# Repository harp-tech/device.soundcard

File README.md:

## Harp Soundcard
This is a high performance sound card with two output channels using 24 bits DACs at 192kHz sample rate. 

### Hardware Compatibility

| HW Version | Board                    | Board HW Version  | Notes                             |
| ---------- | ------------------------ |------------------ | --------------------------------- |
| **All**    | [Peripheral.AudioAmp][1] | >= 2.0            |                                   |

[1]: https://github.com/harp-tech/peripheral.audioamp

### Firmware Compatibility

| FW Version | Board                 | Board HW Version | Notes                                   |
| ---------- | --------------------- | ---------------- | --------------------------------------- |
| **>= 2.2** | [Device.SoundCard][2] | >= 1.0           | Bpod serial communication not supported |
| **<= 2.2** | [Device.SoundCard][2] | >= 1.0           |                                         |

[2]: https://github.com/harp-tech/device.soundcard

### Key Features ###

* Internal memory to store sounds, enabling low-latency sound delivery
* Pre-selected sounds can be triggered using an external TTL
* Internal wave generator allows the user to configure a pure tone without loading a sound file
* Stereo 24 bit @ 192 kHz maximum sampling rate outputs
* THD: -111dB (1 kHz @ 2 V rms)
* Noise Floor:	20 µV rms | -94 dB (20 Hz – 80 kHz)
* SNR:	100 dB | 113 dbA (20 Hz – 80 kHz @ 2 V rms)

### Connectivity ###

* 1x clock sync input (CLKIN) [stereo jack]
* 1x USB (for computer communication) [USB Mini-B]
* 1x micro USB (for sounds loading) [USB Micro-B]
* 1x 12V supply [barrel connector jack]
* 1x reset button [tactile switch]
* 1x output for the left channel [RCA]
* 1x output for the right channel [RCA]
* 3x general purpose digital outputs (3.3V or 5V) (OUT0-OUT2) [screw terminal]
* 3x general purpose digital inputs (5V tolerant) (IN0-IN2) [screw terminal]
* 2x analog inputs (3.3V máx - 5V tolerant) (ADC0-ADC1) [screw terminal]

## Interface ##

The interface with the Harp Soundcard can be done through [Bonsai](https://bonsai-rx.org/) or a dedicated GUI (Graphical User Interface).

### Install Graphical User Interface (GUI) ###

In order to use this GUI, there are some software that needs to be installed:

1 - Install the [drivers](https://bitbucket.org/fchampalimaud/downloads/downloads/UsbDriver-2.12.26.zip).

2 - Install the [runtime](https://bitbucket.org/fchampalimaud/downloads/downloads/Runtime-1.0.zip).

3 - Reboot the computer.

4 - Install the [GUI](https://bitbucket.org/fchampalimaud/downloads/downloads/Harp%20Sound%20Card%20v1.2.1.zip).

### Install Drivers ###

To install the proper drivers to interface with the device, follow the next steps in sequence.

1 - Connect both Harp Sound Card's USB ports to the computer.

2 - Launch the previously installed Harp Sound Card GUI.

3 - Click on the button Open Drivers folder and launch the zadig-2.3.exe.

4 - (1) Select the Harp Sound Card from the list. If the device is not available, go to Options -> List All Devices.

5 - (2) Select the WinUSB driver and click Install WCID Driver.

## Firmware ##

### Tagging Scheme ###

|Tag|Description|
|-|-|
|SoundCard-*|Firmware for the sound card's microcontroller (8 bits processor)|
|SoundCard.PIC32-*|Firmware for the sound card's 32 bits processor|

### Firmware Update ###

1 - Install the [Harp Converto to CSV](https://bitbucket.org/fchampalimaud/downloads/downloads/Harp_Convert_To_CSV_v1.8.3.zip).

2 - Open the Harp Convert to CSV application and write *bootloader* under List box on the Options tab

3 - Select the correspondent COM port and then select the firmware to be loaded for both microcontrollers 

# Licensing #

Each subdirectory will contain a license or, possibly, a set of licenses if it involves both hardware and software.

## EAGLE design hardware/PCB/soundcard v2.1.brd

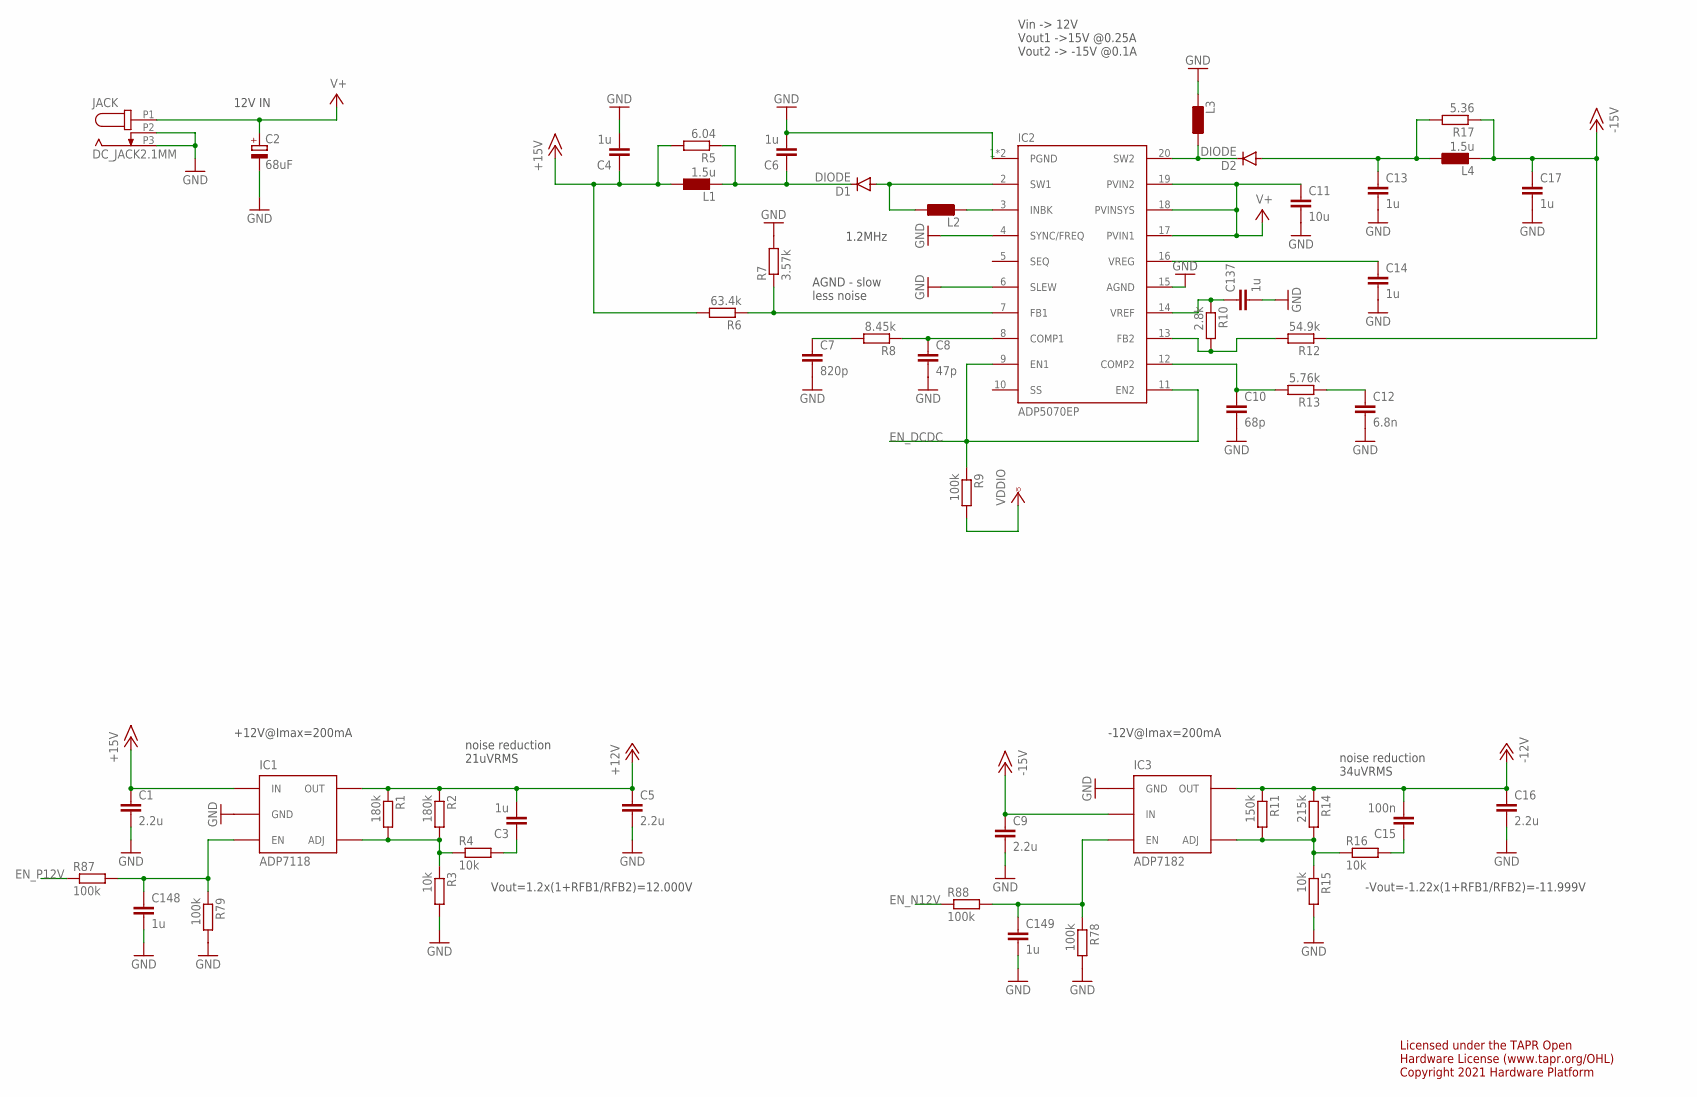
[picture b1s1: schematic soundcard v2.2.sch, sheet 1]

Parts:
C1, C5, C9, C16: 2.2u; C0603
C2: 68uF; E2-5
C3, C14, C137: 1u; C0402
C4, C6, C13, C17, C148, C149: 1u; C0603
C7: 820p; C0402
C8: 47p; C0402
C10: 68p; C0402
C11: 10u; C1206
C12: 6.8n; C0402
C15: 100n; C0402
D1, D2: DIODE; SOD-323-DIODE
IC1: ADP7118; TSOT23-5
IC2: ADP5070EP; TSSOP-EP-20
IC3: ADP7182; TSOT23-5
JACK: DC_JACK2.1MM; DC_POWER_INPUT_2.1MM
L1, L4: 1.5u; IND_LPS4012_V2
L2, L3: INDLPS6225_L; IND_LPS6225_V2
R1, R2: 180k; R0402
R3, R4, R15, R16: 10k; R0402
R5: 6.04; R0402
R6: 63.4k; R0402
R7: 3.57k; R0402
R8: 8.45k; R0402
R9, R78, R79, R87, R88: 100k; R0402
R10: 2.8k; R0402
R11: 150k; R0402
R12: 54.9k; R0402
R13: 5.76k; R0402
R14: 215k; R0402
R17: 5.36; R0402

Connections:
+12V: C3.2, C5.1, IC1.5 (OUT), R1.1, R2.1; also elsewhere on the board
+15V: C1.1, C4.1, IC1.1 (IN), L1.1, R5.2, R6.2
-12V: C15.2, C16.1, IC3.5 (OUT), R11.1, R14.1; also elsewhere on the board
-15V: C9.1, C17.1, IC3.2 (IN), L4.2, R12.1, R17.1
EN_DCDC: IC2.9 (EN1), IC2.11 (EN2), R9.1; also elsewhere on the board
EN_N12V: R88.1; also elsewhere on the board
EN_P12V: R87.1; also elsewhere on the board
GND: C1.2, C2.-, C4.2, C5.2, C6.2, C7.2, C8.2, C9.2, C10.2, C11.2, C12.2, C13.2, C14.2, C16.2, C17.2, C137.2, C148.2, C149.2, IC1.2 (GND), IC2.1 (PGND), IC2.4 (SYNC/FREQ), IC2.6 (SLEW), IC2.15 (AGND), IC2.EPAD (PGND), IC3.1 (GND), JACK.P2 (2), JACK.P3 (3), L3.2, R3.2, R7.2, R15.2, R78.2, R79.2; also elsewhere on the board
INBK: IC2.3 (INBK), L2.2
unnamed: IC2.7 (FB1), R6.1, R7.1
unnamed: C7.1, R8.2
unnamed: C8.1, IC2.8 (COMP1), R8.1
unnamed: C10.1, IC2.12 (COMP2), R13.2
unnamed: C12.1, R13.1
unnamed: C14.1, IC2.16 (VREG)
unnamed: C3.1, R4.2
unnamed: IC2.13 (FB2), R10.2, R12.2
unnamed: C137.1, IC2.14 (VREF), R10.1
unnamed: IC1.4 (ADJ), R1.2, R2.2, R3.1, R4.1
unnamed: IC3.4 (ADJ), R11.2, R14.2, R15.1, R16.1
unnamed: C15.1, R16.2
unnamed: C148.1, IC1.3 (EN), R79.1, R87.2
unnamed: C149.1, IC3.3 (EN), R78.1, R88.2
OUTN15: C13.1, D2.A, L4.1, R17.2
OUTP15: C6.1, D1.C, L1.2, R5.1
OUT_SW1: D1.A, IC2.2 (SW1), L2.1
OUT_SW2: D2.C, IC2.20 (SW2), L3.1
V+: C2.+, C11.1, IC2.17 (PVIN1), IC2.18 (PVINSYS), IC2.19 (PVIN2), JACK.P1 (1); also elsewhere on the board
VCCIO: R9.2; also elsewhere on the board

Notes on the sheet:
Vin -> 12V Vout1 ->15V @0.25A Vout2 -> -15V @0.1A
1.2MHz
AGND - slow less noise
noise reduction 34uVRMS
-12V@Imax=200mA
-Vout=-1.22x(1+RFB1/RFB2)=-11.999V
+12V@Imax=200mA
Vout=1.2x(1+RFB1/RFB2)=12.000V
noise reduction 21uVRMS
Licensed under the TAPR Open Hardware License (www.tapr.org/OHL) Copyright 2021 Hardware Platform
12V IN

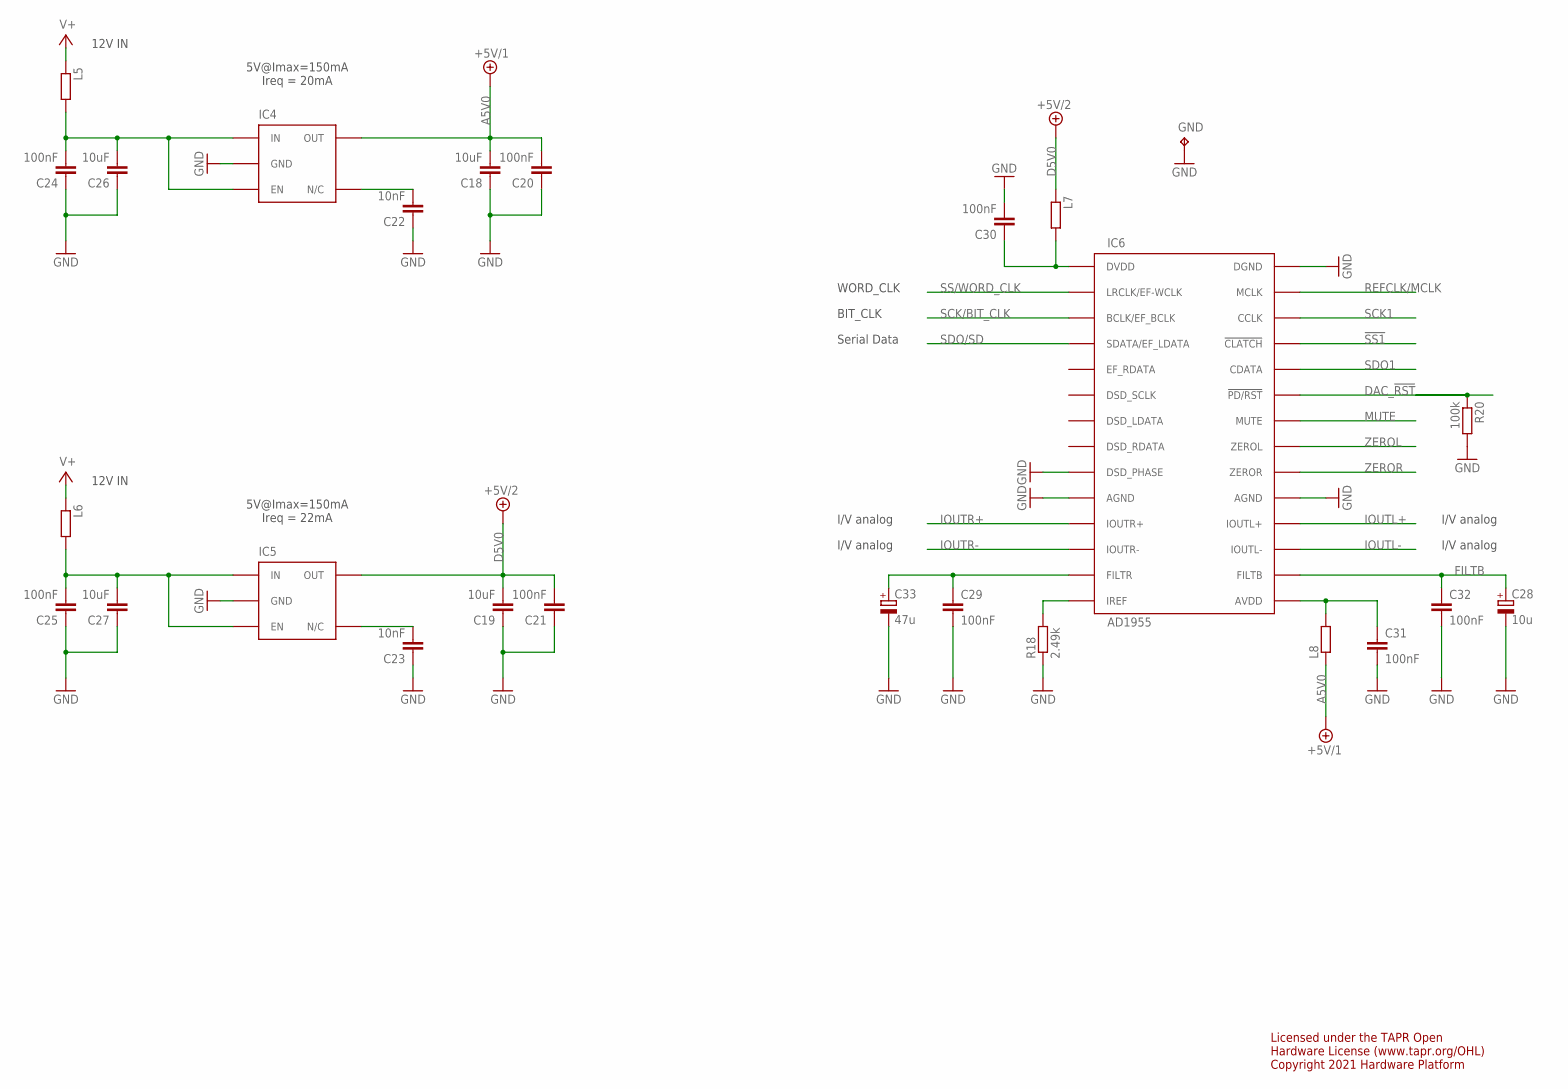
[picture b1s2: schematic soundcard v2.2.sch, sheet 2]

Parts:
C18, C19, C26, C27: 10uF; C0603
C20, C21, C24, C25, C29, C30, C31, C32: 100nF; C0402
C22, C23: 10nF; C0402
C28: 10u; B/3528-21W
C33: 47u; C/6032-28W
GND: TP; TP_1
IC4, IC5: LP5907MFX-3.3; TSOT23-5
IC6: AD1955; SSOP28
L5, L6, L7, L8: 600@100M; R0805
R18: 2.49k; R0402
R20: 100k; R0402

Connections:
!SS1: IC6.P25 (!CLATCH); also elsewhere on the board
A5V0: C18.2, C20.2, IC4.5 (OUT), L8.1; also elsewhere on the board
D5V0: C19.2, C21.2, IC5.5 (OUT), L7.1
DAC_!RST: IC6.P23 (!PD/RST), R20.1; also elsewhere on the board
FILTB: C28.+, C32.1, IC6.P16 (FILTB)
GND: C18.1, C19.1, C20.1, C21.1, C22.1, C23.1, C24.1, C25.1, C26.1, C27.1, C28.-, C29.2, C30.2, C31.2, C32.2, C33.-, GND.TP, IC4.2 (GND), IC5.2 (GND), IC6.P9 (DSD_PHASE), IC6.P10 (AGND), IC6.P19 (AGND), IC6.P28 (DGND), R18.1, R20.2; also elsewhere on the board
IOUTL+: IC6.P18 (IOUTL+); also elsewhere on the board
IOUTL-: IC6.P17 (IOUTL-); also elsewhere on the board
IOUTR+: IC6.P11 (IOUTR+); also elsewhere on the board
IOUTR-: IC6.P12 (IOUTR-); also elsewhere on the board
MUTE: IC6.P22 (MUTE); also elsewhere on the board
unnamed: C22.2, IC4.4 (N/C)
unnamed: C25.2, C27.2, IC5.1 (IN), IC5.3 (EN), L6.2
unnamed: C23.2, IC5.4 (N/C)
unnamed: C30.1, IC6.P1 (DVDD), L7.2
unnamed: C29.1, C33.+, IC6.P13 (FILTR)
unnamed: C31.1, IC6.P15 (AVDD), L8.2
unnamed: IC6.P14 (IREF), R18.2
unnamed: C24.2, C26.2, IC4.1 (IN), IC4.3 (EN), L5.2
REFCLK/MCLK: IC6.P27 (MCLK); also elsewhere on the board
SCK1: IC6.P26 (CCLK); also elsewhere on the board
SCK/BIT_CLK: IC6.P3 (BCLK/EF_BCLK); also elsewhere on the board
SDO1: IC6.P24 (CDATA); also elsewhere on the board
SDO/SD: IC6.P4 (SDATA/EF_LDATA); also elsewhere on the board
SS/WORD_CLK: IC6.P2 (LRCLK/EF-WCLK); also elsewhere on the board
V+: L5.1, L6.1; also elsewhere on the board
ZEROL: IC6.P21 (ZEROL); also elsewhere on the board
ZEROR: IC6.P20 (ZEROR); also elsewhere on the board

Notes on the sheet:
WORD_CLK
BIT_CLK
Serial Data
I/V analog
5V@Imax=150mA Ireq = 20mA
12V IN
Licensed under the TAPR Open Hardware License (www.tapr.org/OHL) Copyright 2021 Hardware Platform
5V@Imax=150mA Ireq = 22mA

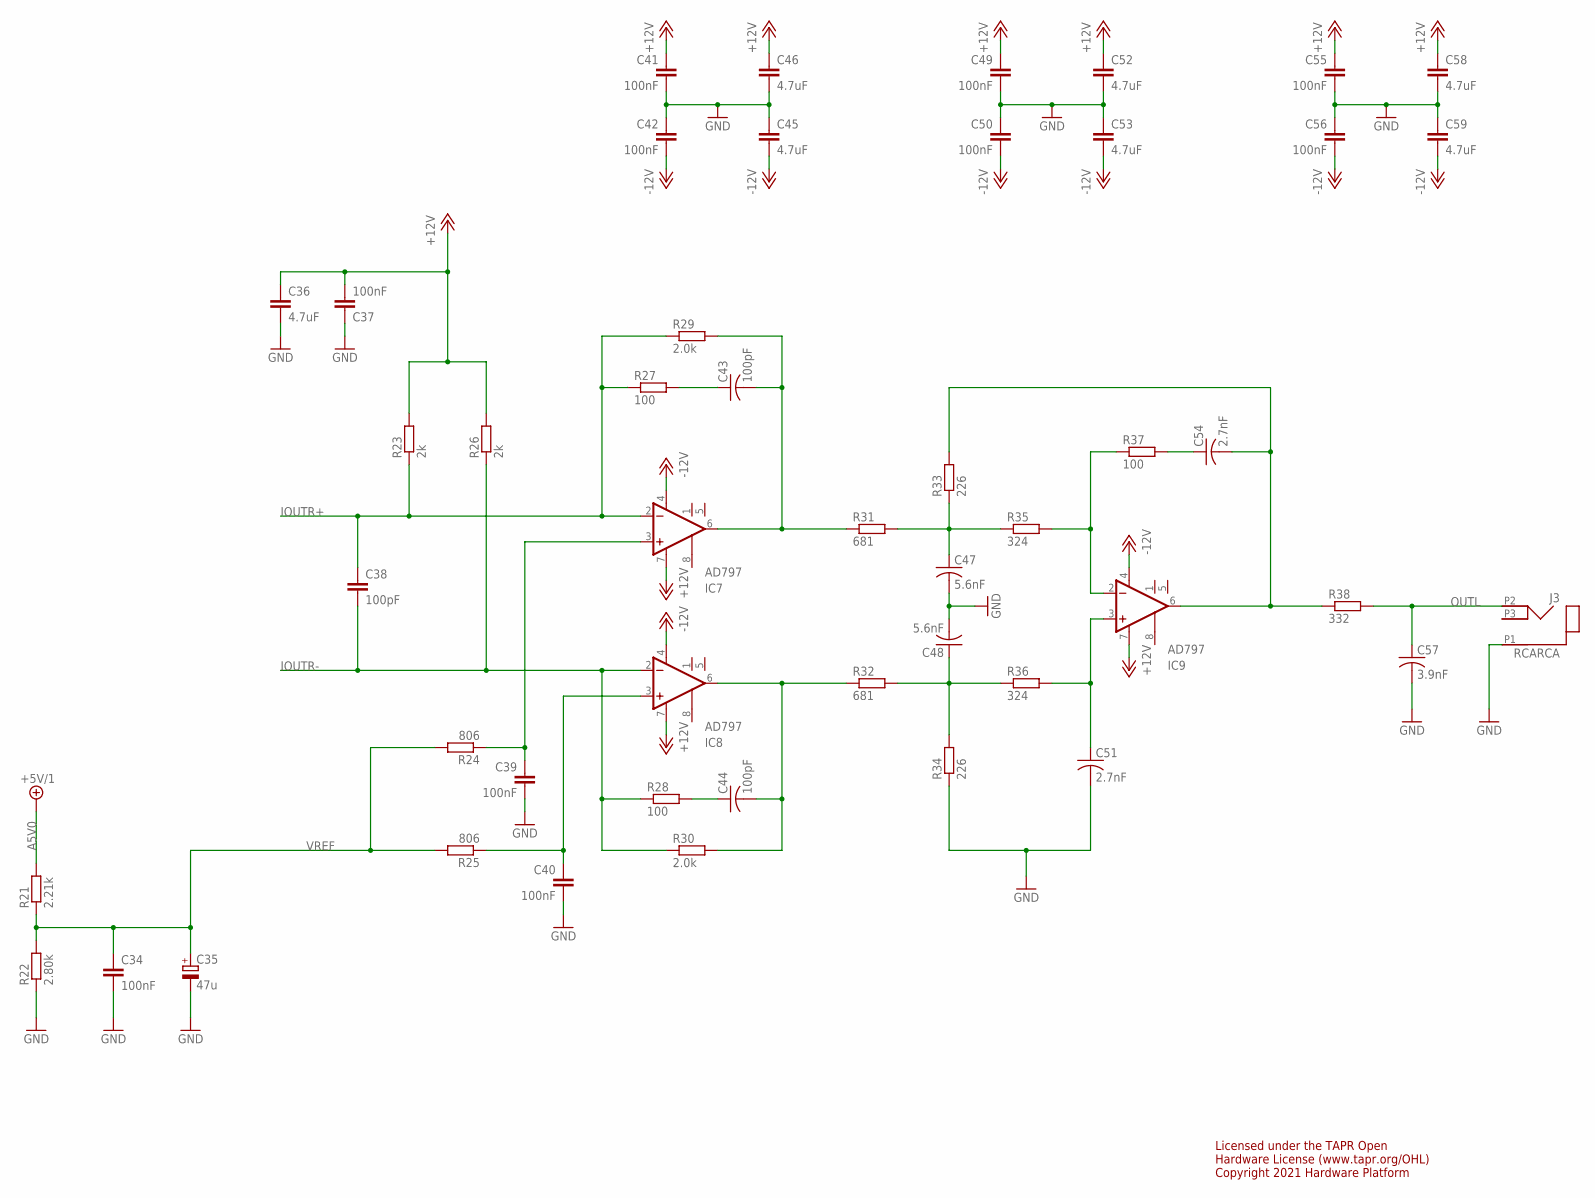
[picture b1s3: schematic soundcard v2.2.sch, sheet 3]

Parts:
C34, C37, C39, C40, C41, C42, C49, C50, C55, C56: 100nF; C0402
C35: 47u; C/6032-28W
C36, C45, C46, C52, C53, C58, C59: 4.7uF; C0603
C38: 100pF; C0603
C43, C44: 100pF; C050-025X075
C47, C48: 5.6nF; C050-025X075
C51, C54: 2.7nF; C050-025X075
C57: 3.9nF; C050-025X075
IC7, IC8, IC9: AD797; SO08
J3: RCARCA; RCA
R21: 2.21k; R0402
R22: 2.80k; R0402
R23, R26: 2k; R0402
R24, R25: 806; R0402
R27, R28, R37: 100; R0402
R29, R30: 2.0k; R0402
R31, R32: 681; R0402
R33, R34: 226; R0402
R35, R36: 324; R0402
R38: 332; R0402

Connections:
+12V: C36.1, C37.2, C41.1, C46.1, C49.1, C52.1, C55.1, C58.1, IC7.7 (V+), IC8.7 (V+), IC9.7 (V+), R23.2, R26.2; also elsewhere on the board
-12V: C42.2, C45.2, C50.2, C53.2, C56.2, C59.2, IC7.4 (V-), IC8.4 (V-), IC9.4 (V-); also elsewhere on the board
A5V0: R21.2; also elsewhere on the board
GND: C34.2, C35.-, C36.2, C37.1, C39.2, C40.2, C41.2, C42.1, C45.1, C46.2, C47.2, C48.2, C49.2, C50.1, C51.2, C52.2, C53.1, C55.2, C56.1, C57.2, C58.2, C59.1, J3.P1 (1), R22.1, R34.1; also elsewhere on the board
IOUTR+: C38.1, IC7.2 (-IN), R23.1, R27.1, R29.1; also elsewhere on the board
IOUTR-: C38.2, IC8.2 (-IN), R26.1, R28.1, R30.1; also elsewhere on the board
unnamed: C39.1, IC7.3 (+IN), R24.1
unnamed: C40.1, IC8.3 (+IN), R25.1
unnamed: C54.1, R37.2
unnamed: C44.2, IC8.6 (OUT), R30.2, R32.1
unnamed: C43.2, IC7.6 (OUT), R29.2, R31.1
unnamed: C47.1, R31.2, R33.1, R35.1
unnamed: C48.1, R32.2, R34.2, R36.1
unnamed: IC9.2 (-IN), R35.2, R37.1
unnamed: C51.1, IC9.3 (+IN), R36.2
unnamed: C54.2, IC9.6 (OUT), R33.2, R38.1
unnamed: C43.1, R27.2
unnamed: C44.1, R28.2
OUTL: C57.1, J3.P2 (2), R38.2
VREF: C34.1, C35.+, R21.1, R22.2, R24.2, R25.2; also elsewhere on the board

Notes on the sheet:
Licensed under the TAPR Open Hardware License (www.tapr.org/OHL) Copyright 2021 Hardware Platform

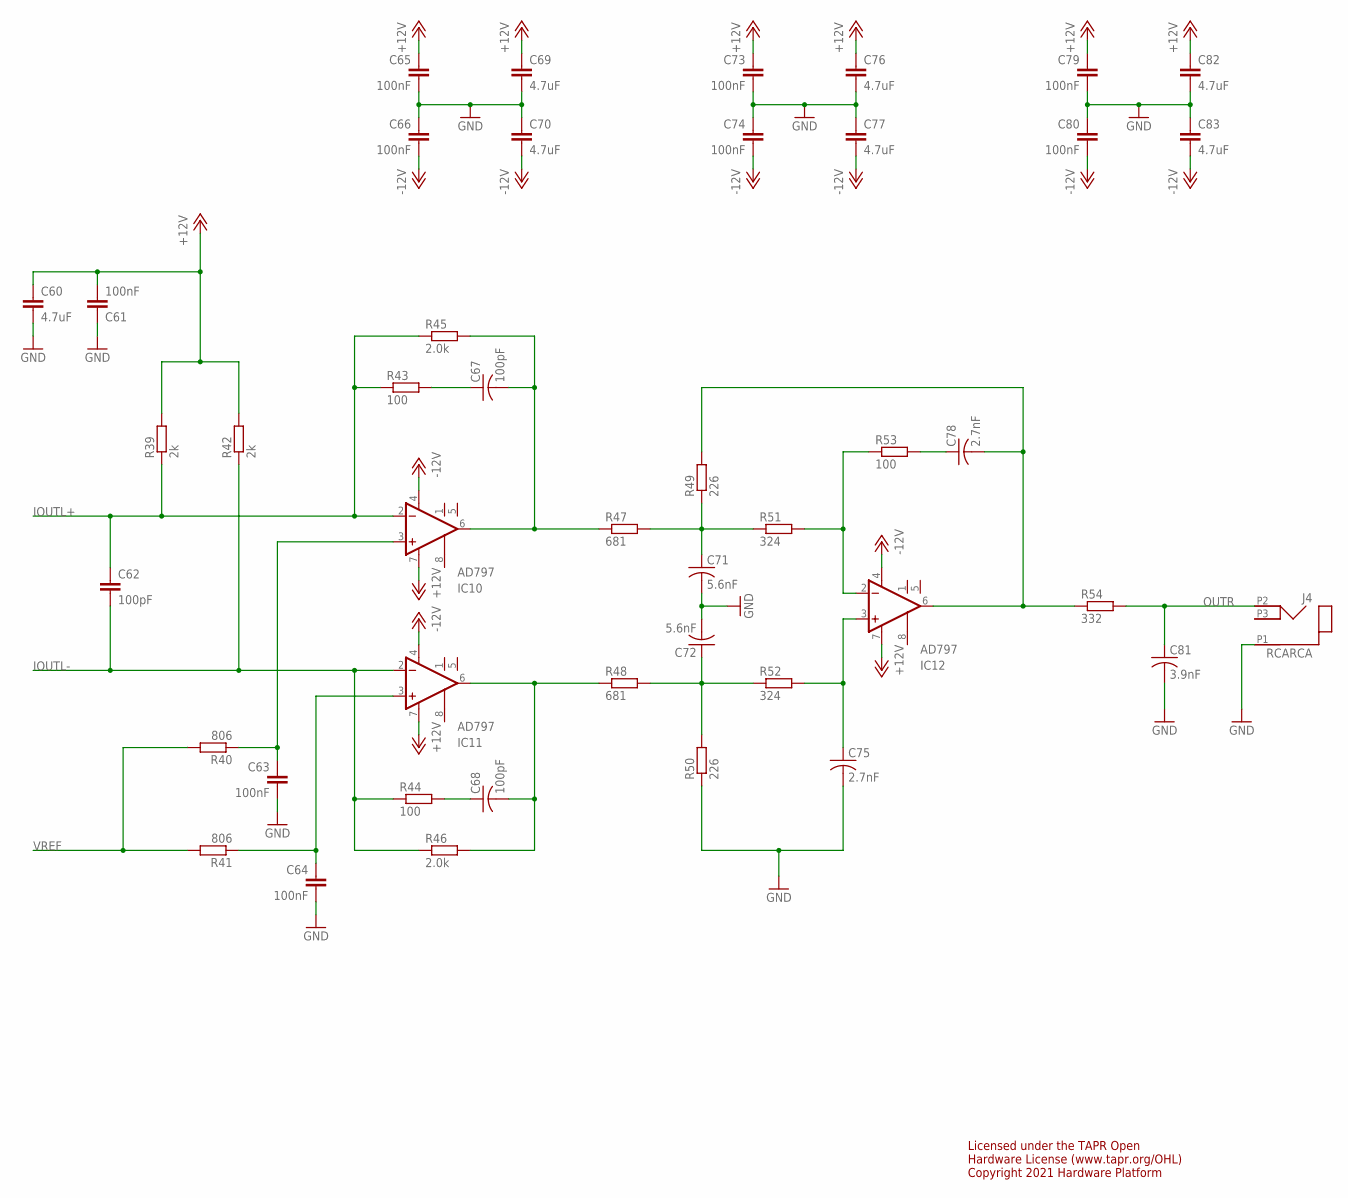
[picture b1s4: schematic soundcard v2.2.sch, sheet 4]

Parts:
C60, C69, C70, C76, C77, C82, C83: 4.7uF; C0603
C61, C63, C64, C65, C66, C73, C74, C79, C80: 100nF; C0402
C62: 100pF; C0603
C67, C68: 100pF; C050-025X075
C71, C72: 5.6nF; C050-025X075
C75, C78: 2.7nF; C050-025X075
C81: 3.9nF; C050-025X075
IC10, IC11, IC12: AD797; SO08
J4: RCARCA; RCA
R39, R42: 2k; R0402
R40, R41: 806; R0402
R43, R44, R53: 100; R0402
R45, R46: 2.0k; R0402
R47, R48: 681; R0402
R49, R50: 226; R0402
R51, R52: 324; R0402
R54: 332; R0402

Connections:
+12V: C60.1, C61.2, C65.1, C69.1, C73.1, C76.1, C79.1, C82.1, IC10.7 (V+), IC11.7 (V+), IC12.7 (V+), R39.2, R42.2; also elsewhere on the board
-12V: C66.2, C70.2, C74.2, C77.2, C80.2, C83.2, IC10.4 (V-), IC11.4 (V-), IC12.4 (V-); also elsewhere on the board
GND: C60.2, C61.1, C63.2, C64.2, C65.2, C66.1, C69.2, C70.1, C71.2, C72.2, C73.2, C74.1, C75.2, C76.2, C77.1, C79.2, C80.1, C81.2, C82.2, C83.1, J4.P1 (1), R50.1; also elsewhere on the board
IOUTL+: C62.1, IC10.2 (-IN), R39.1, R43.1, R45.1; also elsewhere on the board
IOUTL-: C62.2, IC11.2 (-IN), R42.1, R44.1, R46.1; also elsewhere on the board
unnamed: C63.1, IC10.3 (+IN), R40.1
unnamed: C67.2, IC10.6 (OUT), R45.2, R47.1
unnamed: C68.2, IC11.6 (OUT), R46.2, R48.1
unnamed: C71.1, R47.2, R49.1, R51.1
unnamed: C72.1, R48.2, R50.2, R52.1
unnamed: IC12.2 (-IN), R51.2, R53.1
unnamed: C75.1, IC12.3 (+IN), R52.2
unnamed: C78.2, IC12.6 (OUT), R49.2, R54.1
unnamed: C67.1, R43.2
unnamed: C68.1, R44.2
unnamed: C64.1, IC11.3 (+IN), R41.1
unnamed: C78.1, R53.2
OUTR: C81.1, J4.P2 (2), R54.2
VREF: R40.2, R41.2; also elsewhere on the board

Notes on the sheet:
Licensed under the TAPR Open Hardware License (www.tapr.org/OHL) Copyright 2021 Hardware Platform

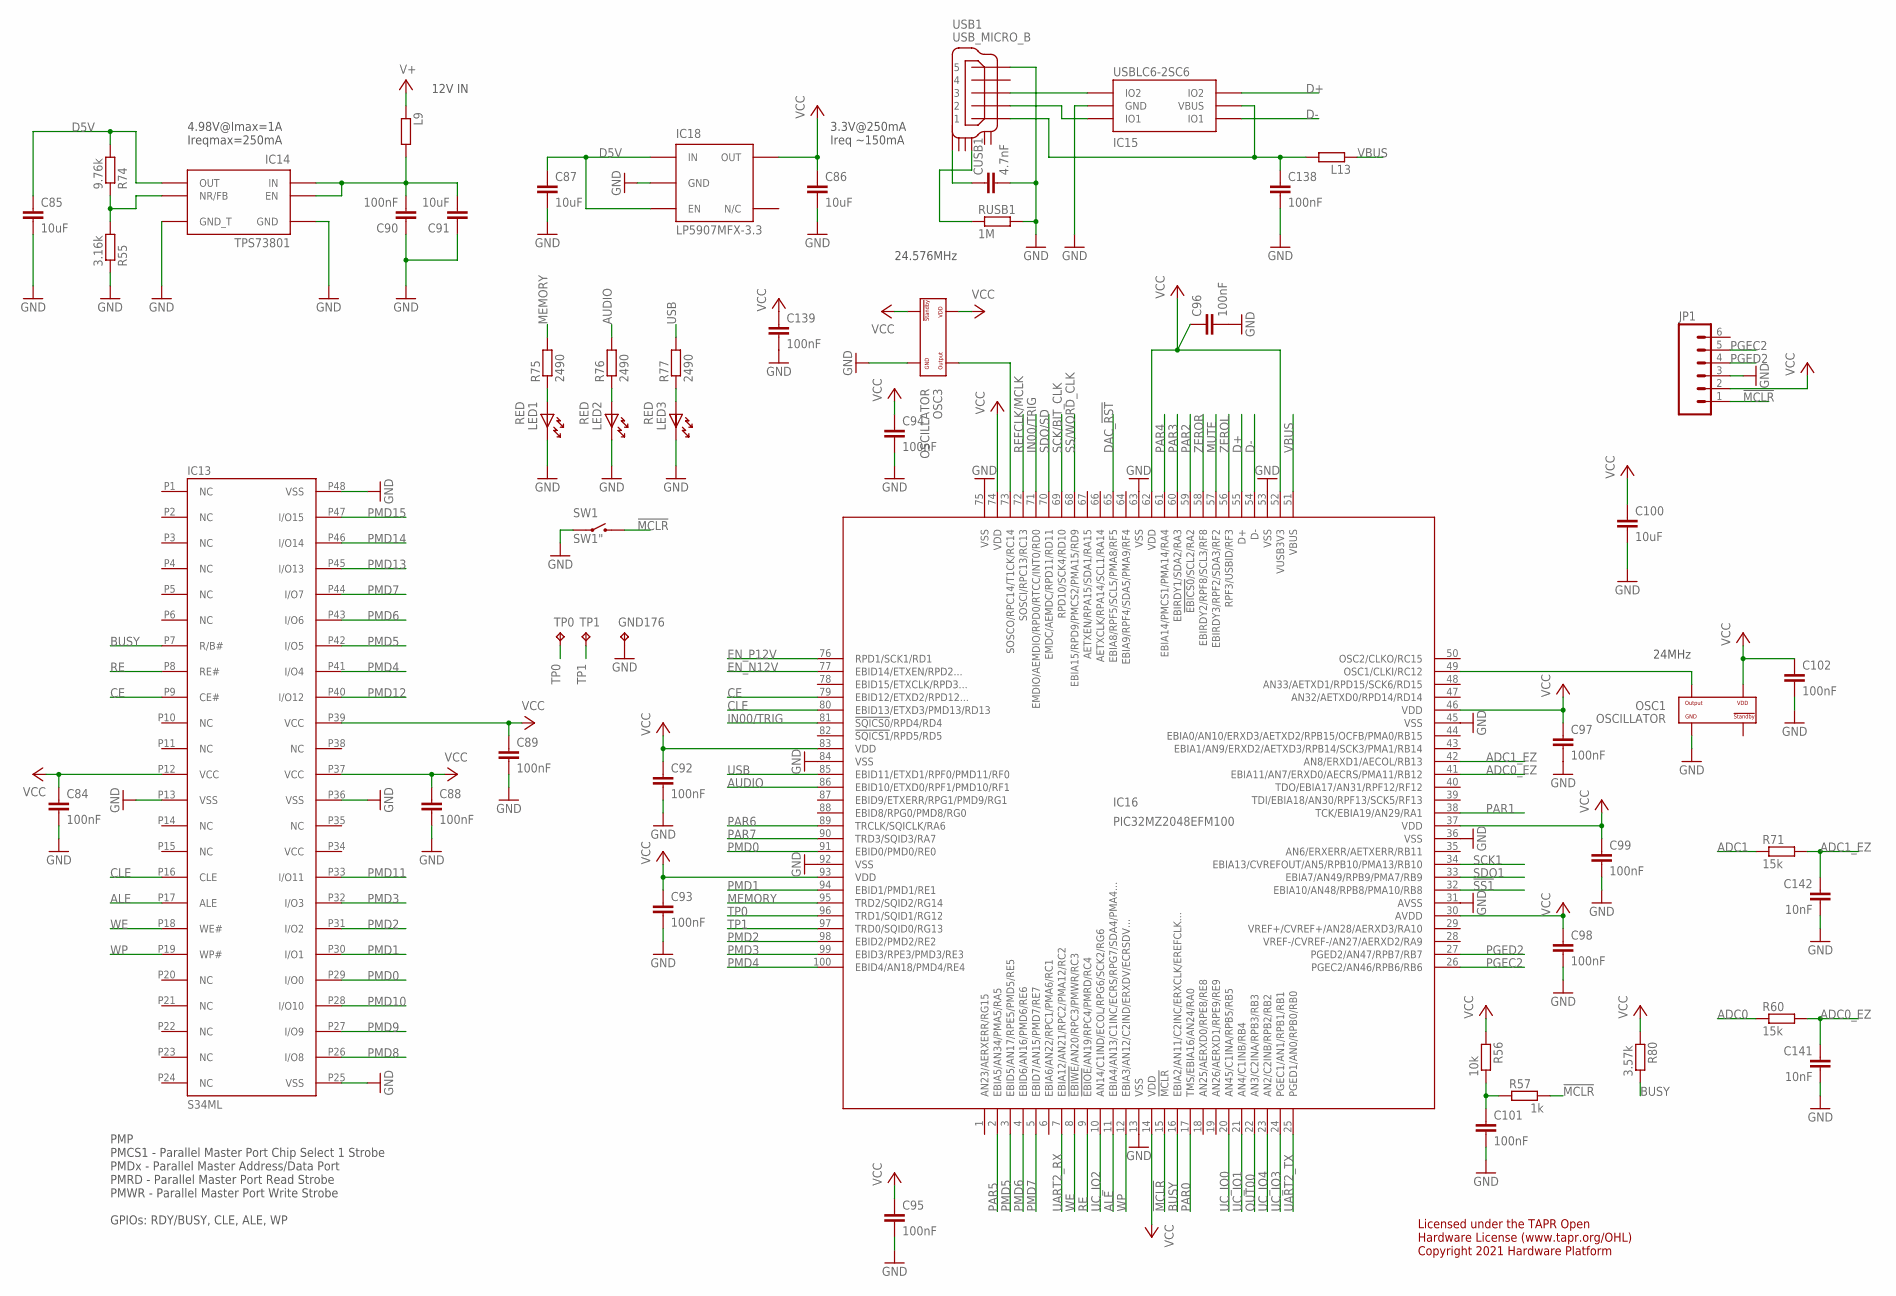
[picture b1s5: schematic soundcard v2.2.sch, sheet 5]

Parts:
C84, C88, C89, C90, C92, C93, C94, C95, C96, C97, C98, C99, C101, C102, C138, C139: 100nF; C0402
C85, C86, C87, C91, C100: 10uF; C0603
C141, C142: 10nF; C0402
CUSB1: 4.7nF; C0402
GND176: TP; TP_1
IC13: S34ML; TSOP-48
IC14: TPS73801; SOT223-6
IC15: USBLC6-2SC6; SOT23-6L
IC16: PIC32MZ2048EFM100; TQFP-100
IC18: LP5907MFX-3.3; TSOT23-5
JP1: M06NO_SILK; 1X06_NO_SILK
L9: 600@100M; R0805
L13: ???; R0805
LED1, LED2, LED3: RED; LED_HAND
OSC1, OSC3: OSCILLATOR; OSCILLATOR_3.2X2.5
R55: 3.16k; R0402
R56: 10k; R0402
R57: 1k; R0402
R60, R71: 15k; R0402
R74: 9.76k; R0402
R75, R76, R77: 2490; R0402
R80: 3.57k; R0402
RUSB1: 1M; R0402
SW1: SW1"; SWITCH_KSS
TP0, TP1: TP; TP_1
USB1: USB_MICRO_B; ZX62D-B-5P8

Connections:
!MCLR: IC16.15 (!MCLR), JP1.1, R57.1, SW1.O
!SS1: IC16.32 (EBIA10/AN48/RPB8/PMA10/RB8); also elsewhere on the board
ADC0: R60.1; also elsewhere on the board
ADC0_EZ: C141.1, IC16.41 (EBIA11/AN7/ERXD0/AECRS/PMA11/RB12), R60.2
ADC1: R71.1; also elsewhere on the board
ADC1_EZ: C142.1, IC16.42 (AN8/ERXD1/AECOL/RB13), R71.2
ALE: IC13.P17 (ALE), IC16.11 (EBIA4/AN13/C1INC/ECRS/RPG7/SDA4/PMA4...)
AUDIO: IC16.86 (EBID10/ETXD0/RPF1/PMD10/RF1), R76.2
BUSY: IC13.P7 (R/B#), IC16.16 (EBIA2/AN11/C2INC/ERXCLK/EREFCLK...), R80.1
CE: IC13.P9 (CE#), IC16.79 (EBID12/ETXD2/RPD12...)
CLE: IC13.P16 (CLE), IC16.80 (EBID13/ETXD3/PMD13/RD13)
D+: IC15.P$4 (IO2), IC16.55 (D+)
D-: IC15.P$6 (IO1), IC16.54 (D-)
DAC_!RST: IC16.65 (EBIA8/RPF5/SCL5/PMA8/RF5); also elsewhere on the board
EN_N12V: IC16.77 (EBID14/ETXEN/RPD2...); also elsewhere on the board
EN_P12V: IC16.76 (RPD1/SCK1/RD1); also elsewhere on the board
GND: C84.2, C85.2, C86.2, C87.2, C88.2, C89.2, C90.1, C91.1, C92.2, C93.2, C94.2, C95.2, C96.2, C97.2, C98.2, C99.2, C100.2, C101.2, C102.2, C138.2, C139.2, C141.2, C142.2, CUSB1.2, GND176.TP, IC13.P13 (VSS), IC13.P25 (VSS), IC13.P36 (VSS), IC13.P48 (VSS), IC14.P$3 (GND), IC14.P$6 (GND_T), IC15.P$2 (GND), IC16.13 (VSS), IC16.31 (AVSS), IC16.36 (VSS), IC16.45 (VSS), IC16.53 (VSS), IC16.63 (VSS), IC16.75 (VSS), IC16.84 (VSS), IC16.92 (VSS), IC18.2 (GND), JP1.3, LED1.K, LED2.K, LED3.K, OSC1.P$2 (GND), OSC3.P$2 (GND), R55.1, RUSB1.2, SW1.P, USB1.P$5 (5); also elsewhere on the board
IN00/TRIG: IC16.71 (EMDIO/AEMDIO/RPD0/RTCC/INT0/RD0), IC16.81 (!SQICS0!/RPD4/RD4); also elsewhere on the board
MEMORY: IC16.95 (TRD2/SQID2/RG14), R75.2
MUTE: IC16.57 (EBIRDY3/RPF2/SDA3/RF2); also elsewhere on the board
unnamed: IC14.P$4 (NR/FB), R55.2, R74.1
unnamed: C90.2, C91.2, IC14.P$1 (IN), IC14.P$5 (EN), L9.2
unnamed: IC16.73 (SOSCO/RPC14/T1CK/RC14), OSC3.P$3 (OUTPUT)
unnamed: LED1.A, R75.1
unnamed: LED2.A, R76.1
unnamed: LED3.A, R77.1
unnamed: IC16.49 (OSC1/CLKI/RC12), OSC1.P$3 (OUTPUT)
unnamed: IC15.P$1 (IO1), USB1.P$2 (2)
unnamed: IC15.P$3 (IO2), USB1.P$3 (3)
unnamed: CUSB1.1, USB1.SHIELD_4
unnamed: RUSB1.1, USB1.SHIELD_3
unnamed: C101.1, R56.1, R57.2
OUT00: IC16.22 (AN3/C2INA/RPB3/RB3); also elsewhere on the board
PAR0: IC16.17 (TMS/EBIA16/AN24/RA0); also elsewhere on the board
PAR1: IC16.38 (TCK/EBIA19/AN29/RA1); also elsewhere on the board
PAR2: IC16.59 (!EBICS0!/SCL2/RA2); also elsewhere on the board
PAR3: IC16.60 (EBIRDY1/SDA2/RA3); also elsewhere on the board
PAR4: IC16.61 (EBIA14/PMCS1/PMA14/RA4); also elsewhere on the board
PAR5: IC16.2 (EBIA5/AN34/PMA5/RA5); also elsewhere on the board
PAR6: IC16.89 (TRCLK/SQICLK/RA6); also elsewhere on the board
PAR7: IC16.90 (TRD3/SQID3/RA7); also elsewhere on the board
PGEC2: IC16.26 (PGEC2/AN46/RPB6/RB6), JP1.5
PGED2: IC16.27 (PGED2/AN47/RPB7/RB7), JP1.4
PMD0: IC13.P29 (I/O0), IC16.91 (EBID0/PMD0/RE0)
PMD1: IC13.P30 (I/O1), IC16.94 (EBID1/PMD1/RE1)
PMD2: IC13.P31 (I/O2), IC16.98 (EBID2/PMD2/RE2)
PMD3: IC13.P32 (I/O3), IC16.99 (EBID3/RPE3/PMD3/RE3)
PMD4: IC13.P41 (I/O4), IC16.100 (EBID4/AN18/PMD4/RE4)
PMD5: IC13.P42 (I/O5), IC16.3 (EBID5/AN17/RPE5/PMD5/RE5)
PMD6: IC13.P43 (I/O6), IC16.4 (EBID6/AN16/PMD6/RE6)
PMD7: IC13.P44 (I/O7), IC16.5 (EBID7/AN15/PMD7/RE7)
PMD8: IC13.P26 (I/O8)
PMD9: IC13.P27 (I/O9)
PMD10: IC13.P28 (I/O10)
PMD11: IC13.P33 (I/O11)
PMD12: IC13.P40 (I/O12)
PMD13: IC13.P45 (I/O13)
PMD14: IC13.P46 (I/O14)
PMD15: IC13.P47 (I/O15)
RE: IC13.P8 (RE#), IC16.9 (!EBIOE!/AN19/RPC4/PMRD/RC4)
REFCLK/MCLK: IC16.72 (SOSCI/RPC13/RC13); also elsewhere on the board
SCK1: IC16.34 (EBIA13/CVREFOUT/AN5/RPB10/PMA13/RB10); also elsewhere on the board
SCK/BIT_CLK: IC16.69 (RPD10/SCK4/RD10); also elsewhere on the board
SDO1: IC16.33 (EBIA7/AN49/RPB9/PMA7/RB9); also elsewhere on the board
SDO/SD: IC16.70 (EMDC/AEMDC/RPD11/RD11); also elsewhere on the board
SS/WORD_CLK: IC16.68 (EBIA15/RPD9/PMCS2/PMA15/RD9); also elsewhere on the board
TP0: IC16.96 (TRD1/SQID1/RG12), TP0.TP
TP1: IC16.97 (TRD0/SQID0/RG13), TP1.TP
UART2_RX: IC16.7 (EBIA12/AN21/RPC2/PMA12/RC2); also elsewhere on the board
UART2_TX: IC16.25 (PGED1/AN0/RPB0/RB0); also elsewhere on the board
UC_IO0: IC16.20 (AN45/C1INA/RPB5/RB5); also elsewhere on the board
UC_IO1: IC16.21 (AN4/C1INB/RB4); also elsewhere on the board
UC_IO2: IC16.10 (AN14/C1IND/ECOL/RPG6/SCK2/RG6); also elsewhere on the board
UC_IO3: IC16.24 (PGEC1/AN1/RPB1/RB1); also elsewhere on the board
UC_IO4: IC16.23 (AN2/C2INB/RPB2/RB2); also elsewhere on the board
USB: IC16.85 (EBID11/ETXD1/RPF0/PMD11/RF0), R77.2
V+: L9.1; also elsewhere on the board
VBUS: IC16.51 (VBUS), L13.1
VBUSX: C138.1, IC15.P$5 (VBUS), L13.2, USB1.P$1 (1)
VCC: C84.1, C86.1, C88.1, C89.1, C92.1, C93.1, C94.1, C95.1, C96.1, C97.1, C98.1, C99.1, C100.1, C102.1, C139.1, IC13.P12 (VCC), IC13.P37 (VCC), IC13.P39 (VCC), IC16.14 (VDD), IC16.30 (AVDD), IC16.37 (VDD), IC16.46 (VDD), IC16.52 (VUSB3V3), IC16.62 (VDD), IC16.74 (VDD), IC16.83 (VDD), IC16.93 (VDD), IC18.5 (OUT), JP1.2, OSC1.P$4 (VDD), OSC3.P$1 (STANDBY#), OSC3.P$4 (VDD), R56.2, R80.2
WE: IC13.P18 (WE#), IC16.8 (!EBIWE!/AN20/RPC3/PMWR/RC3)
WP: IC13.P19 (WP#), IC16.12 (EBIA3/AN12/C2IND/ERXDV/ECRSDV...)
ZEROL: IC16.56 (RPF3/USBID/RF3); also elsewhere on the board
ZEROR: IC16.58 (EBIRDY2/RPF8/SCL3/RF8); also elsewhere on the board

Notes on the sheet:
PMP PMCS1 - Parallel Master Port Chip Select 1 Strobe PMDx - Parallel Master Address/Data Port PMRD - Parallel Master Port Read Strobe PMWR - Parallel Master Port Write Strobe GPIOs: RDY/BUSY, CLE, ALE, WP
12V IN
4.98V@Imax=1A Ireqmax=250mA
3.3V@250mA Ireq ~150mA
24.576MHz
24MHz
Licensed under the TAPR Open Hardware License (www.tapr.org/OHL) Copyright 2021 Hardware Platform

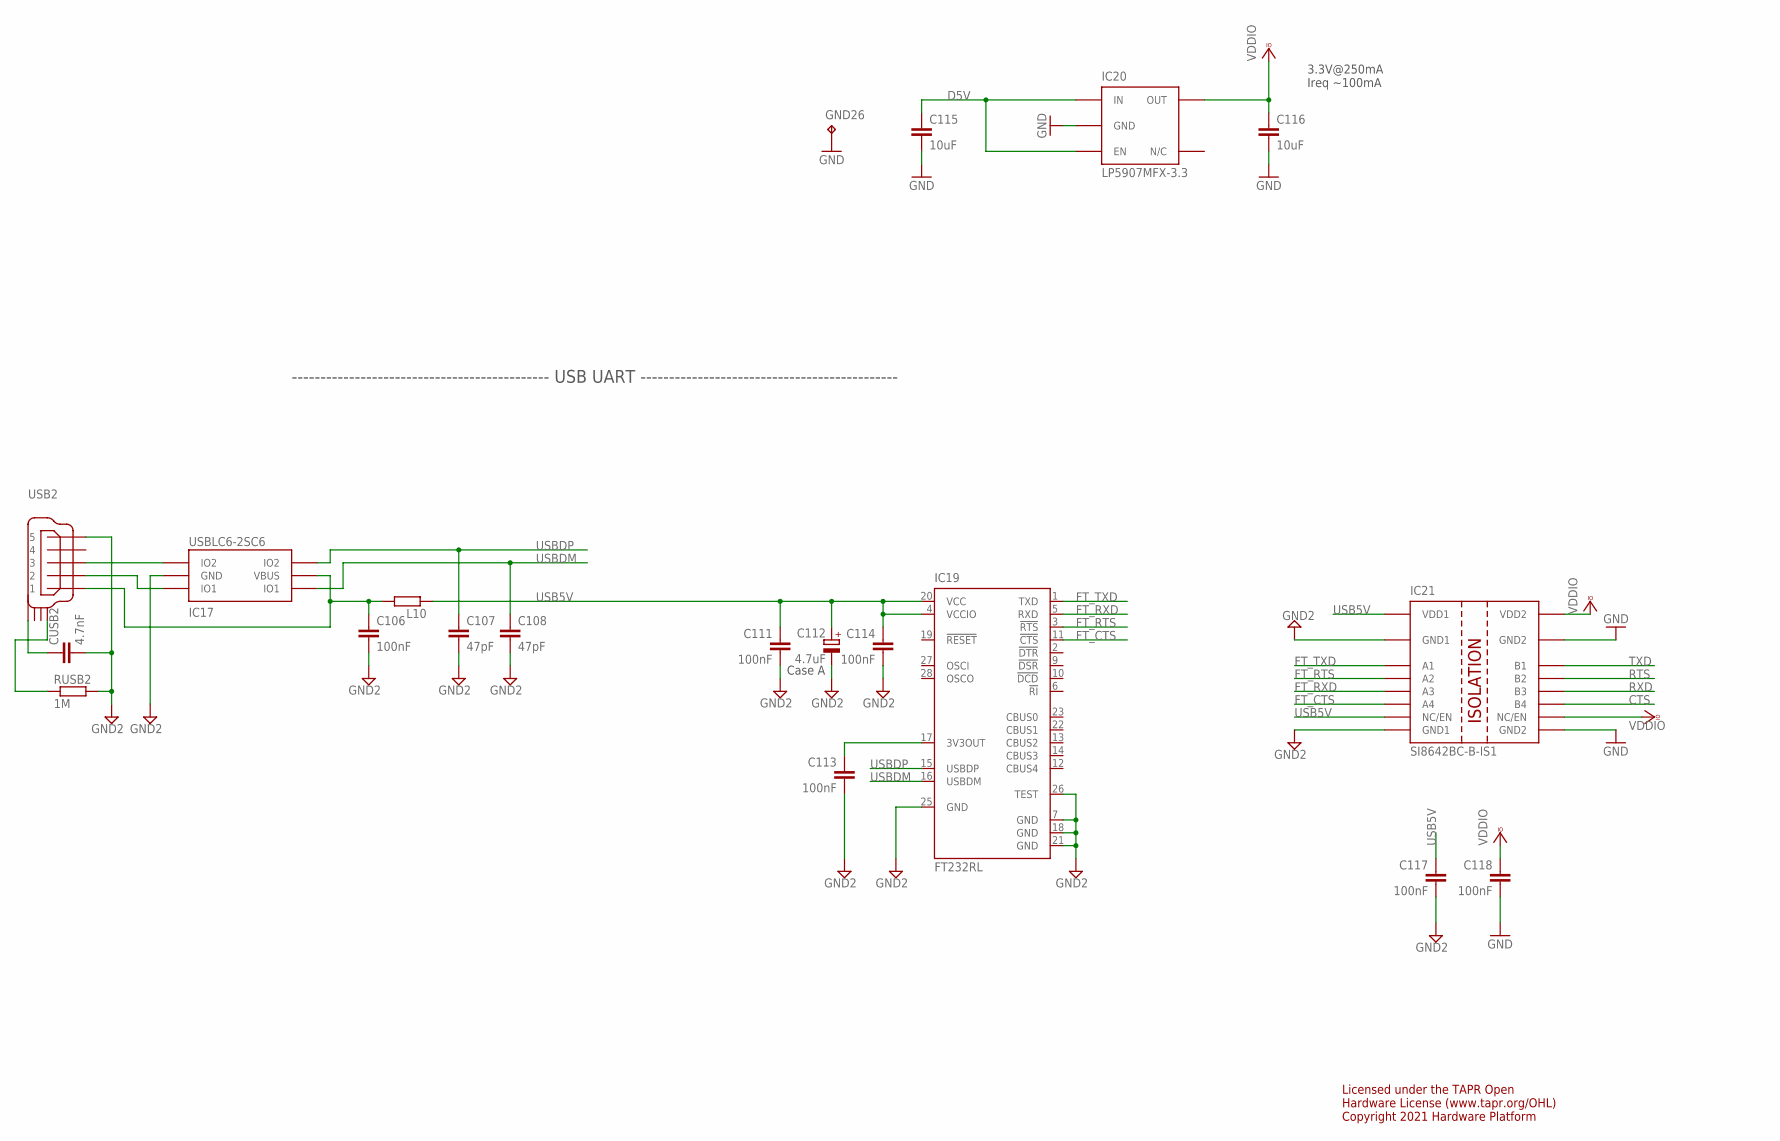
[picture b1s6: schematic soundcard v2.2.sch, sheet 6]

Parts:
C106, C111, C113, C114, C117, C118: 100nF; C0402
C107, C108: 47pF; C0402
C112: 4.7uF; A/3216-18W
C115, C116: 10uF; C0603
CUSB2: 4.7nF; C0402
GND26: TP; TP_1
IC17: USBLC6-2SC6; SOT23-6L
IC19: FT232RL; SSOP28
IC20: LP5907MFX-3.3; TSOT23-5
IC21: SI8642BC-B-IS1; NSOIC-16
L10: ???; R0805
RUSB2: 1M; R0402
USB2: USB_MINI_B; 240-0002-1

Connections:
CTS: IC21.11 (B4); also elsewhere on the board
FT_CTS: IC19.11 (!CTS), IC21.6 (A4)
FT_RTS: IC19.3 (!RTS), IC21.4 (A2)
FT_RXD: IC19.5 (RXD), IC21.5 (A3)
FT_TXD: IC19.1 (TXD), IC21.3 (A1)
GND: C115.2, C116.2, C118.2, GND26.TP, IC20.2 (GND), IC21.9 (GND2), IC21.15 (GND2); also elsewhere on the board
GND2: C106.2, C107.2, C108.2, C111.2, C112.-, C113.2, C114.2, C117.2, CUSB2.2, IC17.P$2 (GND), IC19.7 (GND), IC19.18 (GND), IC19.21 (GND), IC19.25 (GND), IC19.26 (TEST), IC21.2 (GND1), IC21.8 (GND1), RUSB2.2, USB2.P$5 (5)
unnamed: C113.1, IC19.17 (3V3OUT)
unnamed: C106.1, IC17.P$5 (VBUS), L10.2, USB2.P$1 (1)
unnamed: IC17.P$1 (IO1), USB2.P$2 (2)
unnamed: IC17.P$3 (IO2), USB2.P$3 (3)
unnamed: CUSB2.1, USB2.SHIELD_4
unnamed: RUSB2.1, USB2.SHIELD_1
RTS: IC21.13 (B2); also elsewhere on the board
RXD: IC21.12 (B3); also elsewhere on the board
TXD: IC21.14 (B1); also elsewhere on the board
USB5V: C111.1, C112.+, C114.1, C117.1, IC19.4 (VCCIO), IC19.20 (VCC), IC21.1 (VDD1), IC21.7 (NC/EN), L10.1
USBDM: C108.1, IC17.P$6 (IO1), IC19.16 (USBDM)
USBDP: C107.1, IC17.P$4 (IO2), IC19.15 (USBDP)
VCCIO: C116.1, C118.1, IC20.5 (OUT), IC21.10 (NC/EN), IC21.16 (VDD2); also elsewhere on the board

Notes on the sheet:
Case A
--------------------------------------------- USB UART ---------------------------------------------
3.3V@250mA Ireq ~100mA
Licensed under the TAPR Open Hardware License (www.tapr.org/OHL) Copyright 2021 Hardware Platform

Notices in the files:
hardware/PCB/soundcard v2.1.brd:
Copyright 2021 Artur Silva and Filipe Carvalho
parts and their libraries:
SparkFun-Connectors: Licensing: Creative Commons ShareAlike 4.0 International - https://creativecommons.org/licenses/by-sa/4.0
